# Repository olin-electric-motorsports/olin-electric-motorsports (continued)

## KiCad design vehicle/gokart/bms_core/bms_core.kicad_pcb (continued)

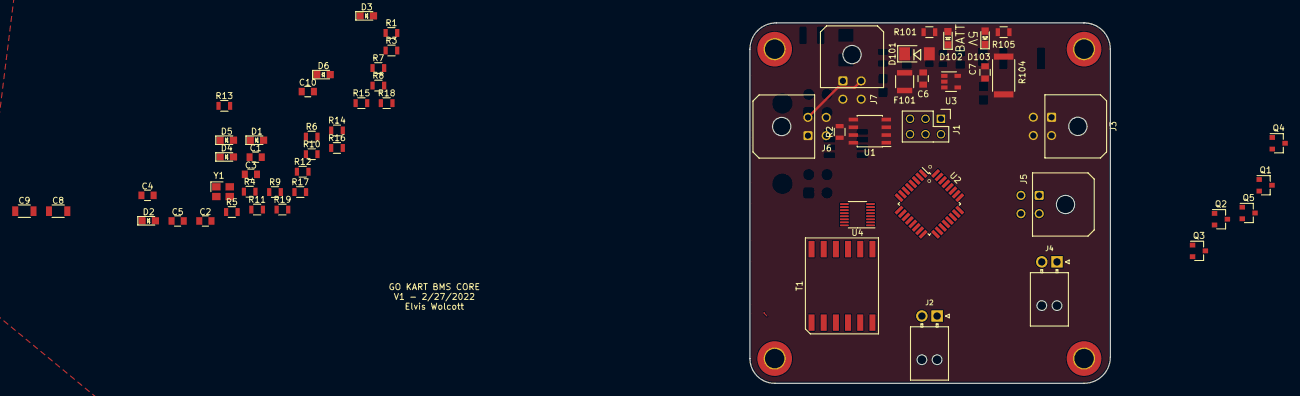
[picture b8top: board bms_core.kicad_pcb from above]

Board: 2 copper layers, 59.2 x 59.2 mm, 60 parts (0 on the bottom side), 47 nets.
